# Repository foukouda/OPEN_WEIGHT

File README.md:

<h1 align="center">OPEN_WEIGHT – AD7190</h1>

<p align="center">
  High-precision load-cell / force measurement PCB based on the AD7190
</p>

<p align="center">
  Sub-project of <a href="https://opentruslab.vercel.app/">OPEN THRUST LAB</a>
</p>

<p align="center" width="100%">

</p>

<p align="center">
  
&nbsp; &nbsp; &nbsp; &nbsp;
  
</p>

<p align="center">
  
  <br><sub>Full-resolution video: <a href="Images/OPEN_WEIGHT.mp4">Images/OPEN_WEIGHT.mp4</a> (KiCad raytracing, <code>kicad-cli pcb render</code>)</sub>
</p>

***

## OVERVIEW

**OPEN_WEIGHT** is an open-hardware measurement board developed as part of **OPEN THRUST LAB**, a community-driven project focused on building open-source test benches for drone motor characterization.

This board is designed around the **Analog Devices AD7190**, a high-resolution 24-bit sigma-delta ADC optimized for precision bridge-sensor and load-cell measurements. Within the Open Thrust Lab ecosystem, OPEN_WEIGHT serves as the dedicated **force / thrust measurement interface**, enabling accurate acquisition from load cells for bench instrumentation and motor performance analysis.

The board requires only a **3.3 V input** from the host system. An onboard TPS61086 boost converter steps this up to 6 V, which is then regulated down to a clean +5 V analog supply by an LT3042 ultralow-noise LDO. This two-stage architecture deliberately trades a small efficiency cost for a significantly cleaner AVDD rail, which directly reduces the measurement noise floor. No external 5 V supply is needed.

The repository is structured as a full hardware project rather than a simple PCB dump. It includes:
- KiCad 10 source files for schematic and PCB layout
- **self-contained libraries**: every symbol, footprint and 3D model used on the board lives in `lib/`
- manufacturing and assembly outputs
- generated schematic and fabrication documentation
- validation reports and test artifacts
- 3D views and project visuals
- automated output generation through **KiBot**
- CI integration for reproducible deliverables

OPEN_WEIGHT is meant to be:
- reproducible
- inspectable
- manufacturable
- easy to iterate on
- aligned with open-hardware development practices

***

## PROJECT CONTEXT

OPEN THRUST LAB is an open-source drone motor test-bench initiative covering hardware, firmware, sensors, data, and analysis. Inside this larger architecture, **OPEN-WEIGHT** is the sub-project dedicated to **precision thrust measurement** — an open-source load-cell amplifier and measurement PCB designed for integration into the bench.

In the broader bench roadmap, this board contributes to the measurement chain used to characterize motor performance through reliable sensor acquisition and fully documented hardware design.

***

## DESIGN GOALS

- Provide a precise measurement front-end for load-cell based force sensing
- Operate entirely from a 3.3 V host rail — no external analog supply required
- Support thrust instrumentation in a modular test-bench architecture
- Expose a clean and reusable KiCad 10 project structure
- Automate hardware deliverables with KiBot and CI
- Make fabrication and assembly easier through fully generated outputs
- Support future revisions, validation, and characterization work

***

## SPECIFICATIONS

### Electrical specifications

| Parameter | Value |
| --- | --- |
| Input voltage (VIN) | 3.3 V (from host system) |
| Boost output — TPS61086 | 6 V |
| Analog supply — LT3042 (AVDD) | 5 V, ultralow-noise |
| Digital supply (DVDD) | 3.3 V (from host) |
| ADC | AD7190, 24-bit sigma-delta |
| PGA gain range | 1 – 128 |
| Voltage reference | Ratiometric: REFIN1± = bridge excitation (EXC+/EXC−) — no separate reference IC |
| Digital interface | SPI — Mode 3 (CPOL=1, CPHA=1), max 5 MHz |
| Additional SPI signal | SYNC — filter reset / multi-device synchronization |
| Clock | 4.9152 MHz ceramic resonator (Y2) on MCLK1/MCLK2 |
| Load cell excitation control | Q1 SI2303 P-MOS high-side switch, gate driven by AD7190 **P3** (GPOCON register); low side through **BPDSW** |
| Sensor type | 2 × 4-wire Wheatstone bridge (AIN1/AIN2 and AIN3/AIN4) |
| Full-scale input (gain 128) | ±VREF/128 = ±39 mV with 5 V excitation |

### Power budget

Power chain: **+3.3 V (host) → TPS61086 → +6 V → LT3042 → +5VA → AD7190**

| Stage | Input rail | Typical current | Typical power |
| --- | --- | --- | --- |
| AD7190 analog (AVDD, gain=128, ODR=10 Hz) | +5VA | ~4 mA | ~20 mW |
| Resonator + RC filters + misc analog | +5VA | ~1 mA | ~5 mW |
| Load cell excitation (4-wire bridge, ~350 Ω) | +5VA | ~14 mA | ~70 mW |
| LT3042 quiescent | +6V | ~2 mA | ~12 mW |
| **LT3042 total input load** | **+6V** | **~21 mA** | **~126 mW** |
| AD7190 digital (DVDD) | +3.3V | ~1 mA | ~3.3 mW |
| TPS61086 input (η ≈ 85–90 % at this load) | **+3.3V** | **~45–50 mA** | **~148–165 mW** |
| **Board total estimated** | **+3.3V** | **~46–51 mA** | **~151–168 mW** |

> **Note:** Load cell excitation current depends on bridge resistance. The estimate above assumes a 350 Ω full bridge at 5 V excitation (~14 mA). A 1000 Ω bridge draws ~5 mA instead, reducing total board consumption significantly. TPS61086 efficiency is estimated from the datasheet curve at Vin=3.3 V, Vout=6 V. Always measure at your specific operating point using the **+3.3V** test point TP4 on Page 4.

### Physical specifications

| Parameter | Value |
| --- | --- |
| Project name | OPEN_WEIGHT |
| Board name | AD7190 |
| Parent project | OPEN THRUST LAB |
| CAD tool | KiCad 10 |
| Automation tooling | KiBot + GitHub Actions |
| Dimensions | 54.0 × 48.0 mm |
| Mounting holes | 4× M3, connected to GND |
| Fiducials | Not fitted on this revision (FID1–FID6 excluded from board) |
| Fabrication target | JLCPCB 4-layer, JLC04161H-7628, 1.6 mm (rules in `OPEN_WEIGHT.kicad_dru`) |
| Repository status | In active development |
| Hardware licence | CERN-OHL-P v2 |

***

## SCHEMATIC ARCHITECTURE

The project is organized into four functional hierarchical sheets (under `Project Architecture`), plus the documentation sheets (Revision History, Block Diagram, Power - Sequencing):

| Page | Sheet (file) | Description |
| --- | --- | --- |
| 4 | `AD7190_Weight_Sensor` (`AD7190 - Weight Sensor.kicad_sch`) | AD7190 24-bit sigma-delta ADC front-end for Wheatstone bridge acquisition. Differential inputs on SENSE± and OUT± lines with RC input filtering. SPI interface (CS, DIN, DOUT, SCLK, SYNC). 4.9152 MHz ceramic resonator (Y2). Ratiometric reference REFIN1 = SENSE± (bridge excitation). Dual-supply decoupling (+5VA analog / +3.3V digital). Q1 P-MOS excitation switch driven by AD7190 P3. Test points on all critical analog and digital nodes. |
| 5 | `Power_Supply` (`Power Supply - Analog Rails.kicad_sch`) | Complete analog power chain, +3.3V (host) → +6V → +5VA. **Boost:** TPS61086 at 1.2 MHz (PWM/PFM via MODE, MODE = GND), integrated 2.0 A / 0.13 Ω switch, external Schottky D3, output set by the FB divider R17/R15 (1.238 V × (1 + 69.8k/18k) = 6.04 V), soft-start C18 and compensation R18/C17. **LDO:** LT3042 ultralow-noise LDO (PSRR > 75 dB) from +6V, +5VA set by RSET = 50 kΩ (ISET = 100 µA), solid tantalum C14 = 2.2 µF on SET for noise (soft-start τ = RSET·CSET = 110 ms), Power-Good via the PGFB divider. Test points: +6V (TP11), +5VA (TP10), SET, PGFB, PG, FB, SS, COMP. |
| 6 | `Holes, Fiducials` (`Holes - Fiducials.kicad_sch`) | Mechanical references for PCB fabrication and assembly. Four GND-connected mounting holes (H1–H4, M3). Fiducial symbols FID1–FID6 are kept in the schematic but excluded from the board on this revision. |
| 7 | `Connectors` (`Connectors.kicad_sch`) | External interface connectors for load cell and host communication. Two 5-pin load-cell connectors J2/J4 (21033213501: OUT, OUT, EXC+, EXC−, GND). 7-pin JST-XH host header J1 (+3.3V, CS, DIN, DOUT/RDY, SYNC, SCLK, GND). WE-SHC shielding frame H5 over the analog front-end. |

***

## SIMULATION (LTspice)

The analog power chain and the ADC input filter are simulated with **LTspice 26** in [`Simulation/LTspice/`](Simulation/LTspice). Every component value comes from the KiCad netlist (reference designators are the same as on the schematic), so the schematics can be opened side by side with the KiCad sheets.

| File | Analysis | What it checks |
| --- | --- | --- |
| `01_Power_Chain_Startup.asc` | `.tran` 600 ms, switching | +3.3V → TPS61086 → +6V → LT3042 → +5VA: boost soft-start, inductor current, +5VA settling to 5 V |
| `02_LT3042_Startup.asc` | `.tran` 1 s | +5VA rise, Power-Good, load-cell excitation turn-on (Q1) |
| `03_Power_Ripple.asc` | `.tran` 6 ms, switching | Boost ripple on +6V and what remains on +5VA (waveform and FFT), input current |
| `04_LT3042_PSRR.asc` | `.ac` 10 Hz – 10 MHz | LT3042 ripple rejection with the board's capacitors |
| `05_AD7190_Input_Filter.asc` | `.ac` 10 Hz – 100 MHz | Differential / common-mode response of the AIN RC filter |

**Models**

- **LT3042**: official Analog Devices model shipped with LTspice.
- **TPS61086**: TI does not provide an LTspice model, so `TPS61086_behav.sub` / `.asy` is a **behavioral model** written for this project from the datasheet (SLVSA05B): 1.2 MHz peak-current-mode PWM, gm = 107 µA/V error amplifier, VREF = 1.238 V, 0.13 Ω switch, 2.6 A current limit, 10 µA soft-start, Power Save Mode (MODE = GND, as on the board). The current-sense gain and slope compensation are not published and are estimated.
- **D3**: PMEG2010AEH modelled with the LTspice PMEG2010EA (same 20 V / 1 A Nexperia MEGA Schottky family). **Q1**: approximate VDMOS model of the SI2303CDS.
- Load on +5VA: AD7190 AVDD (4.5 mA) + one 350 Ω bridge + D4 LED. Ceramic capacitors use nominal values (no DC-bias derating).

**Results**

| Quantity | Simulated | Notes |
| --- | --- | --- |
| +6V output (TPS61086) | 6.037 V | FB divider R17/R15, 1.238 V × (1 + 69.8k/18k) |
| +6V reaches 90 % | 1.1 ms | +6V is precharged to ≈ VIN − VF through L1/D3 before the boost starts |
| +6V start-up overshoot | 6.35 V | well within the LT3042 20 V input rating |
| Peak inductor current at start-up | 1.13 A | below the 2.5 A Isat of L1 |
| +6V ripple, 20 MHz bandwidth | 0.7 mV pp | discontinuous conduction at 1.2 MHz, I(L1) peak ≈ 170 mA; the raw trace shows 35 mV single-sample spikes on the switching edges |
| +5VA ripple, 20 MHz bandwidth | < 1 µV pp | 9 µV pp raw, at the numerical resolution of the simulation |
| +6V spectrum, bridge powered | 194 µV rms at 1.2 MHz | FFT of simulation 03: only the switching frequency and its harmonics (78 / 35 / 20 µV rms); 2.8 µV rms in total from 1 kHz to 1 MHz |
| +5VA spectrum, bridge powered | 5.3 nV rms at 1.2 MHz | 91 dB below +6V, in line with the AC analysis below |
| +6V spectrum in standby (Q1 off) | lines from ≈ 90 kHz, up to 115 µV rms | Power Save Mode: the boost only switches in 46 % of the cycles, which spreads the ripple below 1.2 MHz (231 µV rms from 1 kHz to 1 MHz) |
| LT3042 PSRR at 1.2 MHz | 92 dB | ideal layout; real PSRR at MHz is limited by PCB coupling |
| PG goes high | ≈ 5 ms | end of the LT3042 fast start-up (+5VA = 4.59 V) |
| +5VA after 25 ms / 600 ms | 4.645 V / 4.998 V | complete switching chain (01); after the fast start-up +5VA only rises with τ = RSET·CSET = 110 ms, so a short simulation window shows it below 5 V |
| +5VA reaches 99 % / 99.9 % | 241 ms / 494 ms | complete switching chain (01); 248 ms / 501 ms in 02, where the boost is a 12 ms ramp |
| +5VA dip when Q1 turns on | 29 mV | 350 Ω bridge + SENSE± capacitors switched onto +5VA |
| Bridge excitation V(SENSE+) − V(SENSE−) | 4.955 V | Q1 R<sub>DS(on)</sub> + BPDSW drop |
| Input current from the host (+3.3V) | 66.5 mA | includes D1 (≈ 15 mA) and D4 (≈ 5 mA) LEDs |
| Input filter −3 dB, differential | 2.76 kHz | 350 Ω bridge + 2 × 100 Ω, C28 + C27/C29 |
| Input filter −3 dB, common-mode | 57.9 kHz | 175 Ω + 100 Ω, C27/C29 |
| Differential attenuation at 1.2 MHz | −53 dB | boost switching frequency |

**Re-run the simulations** (Windows, LTspice installed in the default location):

```bash
cd Simulation/LTspice
python run_simulations.py              # runs LTspice in batch mode, redraws Images/Simulation/*.png and results.md
python run_simulations.py --only 03 04 # runs only these simulations, then redraws
python run_simulations.py --no-run     # only redraw from the existing .raw files
```

Or open any `.asc` in LTspice and press *Run*. Simulation 03 switches at 1.2 MHz and takes about a minute. Simulation 01 covers 600 ms of 1.2 MHz switching: about 30 minutes and a 2.8 GB `.raw` file (set `.tran 0 25m` to look at the boost soft-start only, about 1 minute).

> The simulations validate the design intent (regulation, sequencing, filtering). They do not replace bench measurements: layout parasitics, capacitor DC-bias derating and the real TPS61086 control loop will change the ripple figures.

***

## LAYOUT COUPLING (openEMS)

The routed copper is simulated with the **openEMS 0.0.36** field solver (FDTD) in [`Simulation/openEMS/`](Simulation/openEMS), to find what the boost stage leaves on the AD7190 inputs through the layout itself. The four copper layers are taken from the KiCad board and one source of the boost stage is driven at a time:

| Drive | Source | Result |
| --- | --- | --- |
| `sw` | Switch node voltage (IC2 pin 6) | Mutual capacitance to each analog net |
| `loop` | Current of the commutation loop IC2 – D3 – C19/C20 | Mutual inductance to the connector tracks, the input filter and the ADC pins |
| `input` | Current of the input loop C21/C22 – L1 – IC2 | Same |
| `coil` | Current loop of the size of L1, at its place | Same, for the stray field of the inductor |

Each drive is run on the bare board and with the WE-SHC shield H5 fitted with its cover (the frame alone only for the `sw` drive). `measurement_quality.py` then puts these couplings together with the waveforms of LTspice simulation 03 (V(SW) and I(L1), bridge powered) and with the input filter read from the board (R1/R2/R4/R5, C6/C8/C10, C27/C28/C29, a 350 Ω load cell on each connector). The result is the voltage left between the two pins of each ADC input.

**Results**

Worst case: the AD7190 samples its inputs at 307.2 kHz (MCLK / 16) and its digital filter does not reject what falls on a multiple of that rate. 4 × 307.2 kHz = 1.229 MHz is inside the tolerance of the TPS61086 oscillator, so nothing is credited to the digital filter. Away from such a coincidence the digital filter removes the switching frequency altogether.

| Between the two pins of the input, at 1.2 MHz | Bare board | Shield H5 with its cover |
| --- | --- | --- |
| Channel 1 (J4), switch node voltage | 0.04 nV rms | 0.004 nV rms |
| Channel 1 (J4), boost current loops | 3.7 nV rms | 15 nV rms |
| Channel 2 (J2), switch node voltage | 0.2 nV rms | 0.06 nV rms |
| Channel 2 (J2), boost current loops | 38 nV rms | 15 nV rms |
| Reference input (REFIN1), all together | 95 nV rms | 29 nV rms |
| For comparison: noise of the AD7190 itself (4.7 Hz, gain 128) | 8.5 nV rms | 8.5 nV rms |

- Capacitive coupling from the switch node is negligible: 0.006 to 0.06 fF to each analog net on the bare board.
- The path that counts is magnetic. The current loops of the boost stage induce a voltage in the small loop between the capacitor across each pair (C6, C28) and the ADC pins, behind the filter, and around the two capacitors to ground (C8/C10, C27/C29).
- 15 nV is 1.5 ppm of what a 2 mV/V load cell gives at full load under 5 V, and less than twice the noise of the AD7190 itself.
- On the bare board channel 1 (J4) is ten times less exposed than channel 2 (J2), which sits on the side of the boost stage.
- With the cover both channels end up at the same level. What remains comes from the input loop; how it gets under the cover is not identified.
- The reference input sees more, but the reading is a ratio to it: 95 nV on 5 V is 19 ppb.
- L1 is a shielded inductor and its stray field is not published, so it is only bounded, all of its stored energy being taken as stray field: at most 0.9 µV (channel 1) and 2.7 µV (channel 2) on the bare board, 18 nV and 220 nV with the cover. The bound goes with the square root of the share of energy that really leaks. This is the reason to fit the cover.
- Every harmonic up to 250 MHz taken together gives 140 nV (channel 1) and 730 nV (channel 2) on the bare board, 26 nV and 72 nV with the cover. This is a ceiling: the input stage of the AD7190 does not follow tens of MHz, and the LTspice switch commutates in no time.
- A 0.15 mm mesh instead of 0.2 mm changes the commutation loop result by −5 % on channel 1 and +27 % on channel 2.

The complete tables are in [`Simulation/openEMS/results.md`](Simulation/openEMS/results.md).

<p align="center">
  
  <br><sub>Field over time: <a href="Images/Simulation/openems_sw_efield.mp4">Images/Simulation/openems_sw_efield.mp4</a></sub>
</p>

**Re-run the simulation** (Windows, openEMS and its Python 3.11 environment installed in `C:\openEMS`):

```bash
cd Simulation/openEMS
"C:\Program Files\KiCad\10.0\bin\python.exe" export_kicad_geometry.py   # copper of the board -> geometry.json
C:\openEMS\venv\Scripts\python.exe sw_coupling.py --check               # mesh the board and verify the nets
C:\openEMS\venv\Scripts\python.exe sw_coupling.py --case open           # the four drives on the bare board
C:\openEMS\venv\Scripts\python.exe sw_coupling.py --case shield         # the same with the cover
C:\openEMS\venv\Scripts\python.exe measurement_quality.py               # results.md and the figure
```

One run meshes 1.85 M cells and takes about 13 minutes on 8 cores. `measurement_quality.py` needs the `.raw` file of LTspice simulation 03.

> Not modelled: the load cell and its cable, the connectors above the board, the package of the AD7190. Fitted parts are wires at the mid height of their body and the boost waveforms come from a behavioral model, so expect a factor 2 to 3 on these figures. A bench measurement of the ADC noise with the boost running and stopped remains the reference.

***

## LOAD CELL CONNECTION

The board accepts any standard **4-wire Wheatstone bridge** load cell.

### Load-cell connectors J2 / J4 (21033213501, 5 pins)

| Pin | Net (J4 / J2) | Function |
| --- | --- | --- |
| 1 | IN-OUT+ / IN-OUT+2 | Bridge signal output (through 100 Ω + RC filter) |
| 2 | IN-OUT− / IN-OUT−2 | Bridge signal output (through 100 Ω + RC filter) |
| 3 | SENSE+ | Excitation + (switched +5VA from Q1) and REFIN1(+) |
| 4 | SENSE− | Excitation − (AD7190 BPDSW low-side switch) and REFIN1(−) |
| 5 / shell | GND | Cable shield |

J4 → AIN1/AIN2, J2 → AIN3/AIN4. Both channels measure **V(pin 2) − V(pin 1)**: if the load reads negative, swap the signal wires or invert the sign in firmware.

> ⚠️ Load cell cable colors vary by manufacturer. Always verify EXC± and SIG± with a multimeter **before** powering the board.

> ⚠️ The excitation is switched by **Q1 (P-MOS)** whose gate is driven by the AD7190 **P3** pin. Enable it through the GPOCON register (GP32EN = 1, P3DAT = 0 → Q1 on). Do not enable excitation during internal calibration.

### Compatible load cell characteristics

- Differential output: **0 – 20 mV/V** at rated excitation
- Bridge resistance: **120 Ω to 1000 Ω** full bridge
- Ratiometric measurement: with gain 128 and 5 V excitation, full-scale input = ±5 V / 128 = **±39 mV**

### Host header J1 (JST-XH B7B-XH-AM, 7 pins)

| Pin | Signal | Direction | Notes |
| --- | --- | --- | --- |
| 1 | +3.3V | Power in | Board supply (boost input + AD7190 DVDD) |
| 2 | CS | Input | Active low (100 kΩ pull-up R8) |
| 3 | DIN | Input | Serial data to AD7190 (100 Ω series, RN1) |
| 4 | DOUT/RDY | Output | Serial data from AD7190; also goes low when a conversion is ready |
| 5 | SYNC | Input | Active low — resets the digital filter; tie high if unused |
| 6 | SCLK | Input | SPI clock, max 5 MHz |
| 7 | GND | — | Common ground |

> ⚠️ SPI Mode 3 only (CPOL=1, CPHA=1). There is no separate DRDY pin: poll DOUT/RDY with CS low.

***

## STARTUP SEQUENCE

After 3.3 V is applied, allow the following stages to complete before issuing any SPI command
(see schematic page 8, *Power - Sequencing*; values from the [LTspice simulations](#simulation-ltspice)):

| Stage | Duration | Indicator |
| --- | --- | --- |
| TPS61086 boost start-up (C18 soft-start) | +6V at 90 % after ~1.1 ms, settled after ~2 ms (short 6.35 V overshoot) | +6V reaches 6.04 V (TP11) |
| LT3042 fast start-up (2 mA into CSET while PGFB < 300 mV) | +5VA reaches 4.59 V after ~5 ms | PG (TP17) goes high at 4.59 V |
| LT3042 final settling (RSET 50 kΩ × CSET 2.2 µF = τ 110 ms) | 99 % after ~250 ms, 99.9 % after ~500 ms | +5VA (TP10) |
| **Minimum safe delay** | **≥ 600 ms** from power-on | +5VA settled |

> PG goes high long before +5VA is settled: it only indicates the end of the fast start-up phase. Use the delay, not PG, before calibrating.

> To start faster, reduce C14 (e.g. 0.47 µF → τ = 23.5 ms) at the cost of slightly higher low-frequency noise.

After the delay, the recommended initialization sequence is:

```
1. Issue AD7190 serial reset: assert CS̄, write 40+ bytes of 0xFF on DIN
2. Write CONF register (gain, reference, chop settings)
3. Write MODE register (filter, ODR)
4. Run internal zero-scale calibration — wait for DRDȲ
5. Run internal full-scale calibration — wait for DRDȲ
6. Enable load cell excitation: GPOCON GP32EN=1, P3DAT=0 (Q1 on)
7. Run system calibration with known reference weight
8. Enter continuous conversion mode
```

***

## CALIBRATION

Two levels of calibration are required. Both must be repeated after every power cycle.

### 1. Internal calibration

Corrects the ADC's own offset and gain. Requires no external weights. Must be re-run after any change to PGA gain or ODR.

```
Write MODE register: MD[2:0] = 0b001  (internal zero-scale)
→ Wait for DRDȲ to go low

Write MODE register: MD[2:0] = 0b010  (internal full-scale)
→ Wait for DRDȲ to go low

Results are saved in the ZERO and FULLSCALE registers.
Read them back to cache for faster subsequent startups.
```

### 2. System calibration

Maps ADC output codes to physical units. Repeat any time the mechanical setup changes.

```
1. Remove all load → average ≥16 samples → raw_zero
2. Apply known weight W_ref → average ≥16 samples → raw_full
3. scale_factor = W_ref / (raw_full − raw_zero)
4. weight = (raw_code − raw_zero) × scale_factor
```

### Recommended register configuration

| Register | Field | Value | Reason |
| --- | --- | --- | --- |
| `CONF` | GAIN[2:0] | `0b111` (128×) | Maximizes resolution for low-sensitivity load cells |
| `CONF` | REFSEL | `0b0` | REFIN1± = bridge excitation (ratiometric) |
| `CONF` | CHOP | `1` | Reduces offset and drift |
| `MODE` | SINC | `0b11` (SINC4) | Best 50/60 Hz rejection |
| `MODE` | FS[9:0] | `0x1E0` (480) | fADC = 4.9152 MHz / (1024 × FS) ≈ 10 Hz without chop — rejects 50/60 Hz (with CHOP=1 the rate is lower, see datasheet) |

> ⚠️ After any change to GAIN, ODR, or filter settings, the sigma-delta pipeline resets. Always re-run internal calibration before taking measurements.

> ⚠️ At gain 128 with the 5 V ratiometric reference: full-scale input range = **±39 mV**. A 2 mV/V load cell at 5 V gives 10 mV at full load.

***

## HOW TO USE

### Prerequisites

- **KiCad 10** (files are saved in KiCad 10 format and cannot be opened with KiCad 9 or earlier)
- Nothing else: all symbols, footprints and 3D models are in `lib/` and referenced relative to the project (`KIPRJMOD`, project-local `sym-lib-table` / `fp-lib-table`)
- **KiBot** for automated output generation
- **Docker** recommended for reproducible local CI runs
- Debian/Ubuntu or equivalent environment

### Generate outputs locally

```bash
# Default configuration
./kibot_launch.sh

# Specific variant
./kibot_launch.sh -v CHECKED
```

| Variant | Outputs | ERC/DRC | Typical use |
| --- | --- | --- | --- |
| `DRAFT` | Schematic only | — | Early design work |
| `PRELIMINARY` | Schematic + PCB | — | Layout iterations |
| `CHECKED` | Full | ✓ enforced | Design review, PR validation |
| `RELEASED` | Full | ✓ enforced | Tagged version releases |

### Use a manufactured board

```c
// --- After >= 600 ms from 3.3V power-on (LT3042 soft-start, see page 8) ---

// 1. Reset
ad7190_reset();                            // 40× 0xFF on DIN

// 2. Configure
ad7190_write_reg(REG_CONF,
    CONF_GAIN_128 | CONF_CHOP | CONF_REFSEL_REFIN1);
ad7190_write_reg(REG_MODE,
    MODE_SINC4 | MODE_FS_10HZ);

// 3. Internal calibration
ad7190_write_reg(REG_MODE, MODE_INT_ZERO_CAL);
while (drdy_is_high());
ad7190_write_reg(REG_MODE, MODE_INT_FULL_CAL);
while (drdy_is_high());

// 4. Enable load cell excitation
ad7190_write_reg(REG_GPOCON, GPOCON_GP32EN); // P3 = 0 -> Q1 on

// 5. System calibration
uint32_t raw_zero = ad7190_average(16);    // No load
apply_reference_weight();
uint32_t raw_full = ad7190_average(16);
float scale = W_ref / (float)(raw_full - raw_zero);

// 6. Continuous measurement
ad7190_write_reg(REG_MODE, MODE_CONTINUOUS);
while (1) {
    while (drdy_is_high());
    uint32_t raw = ad7190_read_data();
    float weight = (raw - raw_zero) * scale;
}
```

***

## REPOSITORY CONTENT

| Content | Description |
| --- | --- |
| Schematic sources | KiCad hierarchical schematic — 10 sheets |
| PCB layout | KiCad PCB with all production layers |
| Manufacturing | Gerbers, drill tables, BoM, pick-and-place files |
| Validation | ERC/DRC reports, test-point tables |
| 3D exports | STEP files and rendered views |
| Documentation sheets | Block diagram, architecture, power sequencing, revision history |
| CI resources | GitHub Actions workflows, KiBot YAML configurations |
| Computations | Design notes, filter and power budget calculations |
| Simulation | LTspice simulations of the power chain and ADC input filter, openEMS simulation of the layout coupling |

***

## DIRECTORY STRUCTURE

    .
    ├─ Computations       # Design notes, formulas, and power budget calculations
    ├─ HTML               # Generated HTML pages and web outputs
    ├─ Images             # Pictures, renders, and visual assets
    │
    ├─ kibot_resources    # External resources used by KiBot
    │  ├─ colors          # Color themes for KiCad outputs
    │  ├─ fonts           # Fonts used in generated documents
    │  ├─ scripts         # Helper scripts used with KiBot
    │  └─ templates       # Templates for KiBot reports and generated outputs
    │
    ├─ kibot_yaml         # KiBot YAML configuration files
    ├─ KiRI               # KiRI PCB diff viewer files
    │
    ├─ lib                # Project libraries (self-contained)
    │  ├─ lib_sym         # OPEN_WEIGHT.kicad_sym — every symbol used
    │  ├─ lib_fp          # OPEN_WEIGHT.pretty — every footprint used
    │  └─ 3d_models       # STEP models referenced by the footprints
    │
    ├─ Logos              # Project logos and branding assets
    │
    ├─ Manufacturing
    │  ├─ Assembly        # BoM, position files, assembly notes
    │  └─ Fabrication     # Gerbers, drill tables, fabrication notes
    │     ├─ Drill Tables
    │     └─ Gerbers
    │
    ├─ Mechanical         # Enclosure / support CAD (STEP; SolidWorks & STL kept local)
    ├─ Report             # ERC / DRC reports and validation outputs
    ├─ Schematic          # Exported schematic PDFs
    ├─ Simulation
    │  ├─ LTspice         # LTspice schematics, TPS61086 behavioral model, run/plot script
    │  └─ openEMS         # Field-solver model of the routed copper, coupling to the ADC inputs
    ├─ Templates          # Drawing sheets and title block templates
    ├─ Testing
    │  └─ Testpoints      # Test point tables and documentation
    │
    └─ Variants           # Outputs for project / assembly variants

***

## DEVELOPMENT WORKFLOW

This project uses a reproducible hardware workflow based on **KiCad 10**, **KiBot**, and **GitHub Actions**.

The CI pipeline (`.github/workflows/ci.yaml`) runs KiBot on every push to `dev` or `main` and commits the generated outputs back ("Update Outputs" commits). **Always `git pull` after the CI has run, before editing the project again**, otherwise the regenerated files (`.kicad_pro`, BoM, netlist, README…) will conflict.

> ℹ️ `README.md` is **generated** by KiBot from `kibot_resources/templates/readme.txt`. Edit the template, not `README.md`, or your changes will be overwritten by the next CI run.

**Branch convention:**
- `dev` — development branch, all work branches off here
- Feature branches: `feat/description`
- Fix branches: `fix/description`
- `main` — only receives merges from `dev`; releases are tagged here

**Project metadata** (project name, board name, company, designer, logo, repository URL) is defined once in `kibot_yaml/kibot_main.yaml` (`definitions:` section) and propagated to title blocks, documents and this README.

**Release a new hardware revision:**

1. On `dev`, fill the `[Unreleased]` section of [CHANGELOG.md](CHANGELOG.md) (Added / Changed / Fixed / Removed).
2. Merge `dev` into `main`: `git checkout main && git pull && git merge dev && git push`
3. Tag with a plain semantic version (**no `v` prefix**, the CI only matches `X.Y.Z`): `git tag 1.0.0 && git push origin 1.0.0`
4. The CI builds the `RELEASED` variant, publishes a GitHub Release with fabrication files, and moves `[Unreleased]` to the new version in `CHANGELOG.md`.
5. Re-sync `dev`: `git checkout main && git pull && git checkout dev && git merge main`

***

## TROUBLESHOOTING

| Symptom | Likely cause | Fix |
| --- | --- | --- |
| Output stuck at 0 or inverted | EXC± wiring error | Verify bridge polarity with multimeter |
| Output always at full-scale | SIG+ / SIG− swapped | Swap the two signal wires |
| Garbage SPI readings | SPI mode mismatch | Set host to Mode 3 (CPOL=1, CPHA=1) |
| Readings drift over time | No internal cal after power-on | Re-run zero-scale + full-scale internal calibration |
| DOUT/RDY never goes low | Resonator not oscillating | Reflow Y2 (4.9152 MHz resonator) |
| SPI reads 0xFF | CS̄ stuck high or SCLK too fast | Check CS̄ GPIO; reduce SCLK to ≤ 5 MHz |
| 50/60 Hz interference | ODR too high or wrong filter | Use SINC4 + FS = 0x00A (10 Hz ODR) |
| +5VA absent at power-on | TPS61086 not switching | Verify +3.3V_IN; check inductor L1 solder joints |
| +5VA present but noisy | LT3042 SET pin cap issue | Reflow solid tantalum cap on SET pin (Page 5) |
| No excitation on load cell | Q1 off | Write GPOCON: GP32EN = 1, P3DAT = 0 |
| First readings drift for ~0.5 s | +5VA still rising (τ = 110 ms) | Wait ≥ 600 ms after power-up before calibration |
| Offset drifts after warmup | Thermal settling | Allow 5–10 min warmup; re-tare before measurements |

***

## CONTRIBUTING

Contributions are welcome — hardware corrections, documentation improvements, firmware examples, and validation reports all add value to the project.

### Requirements

- **KiCad 10** — not backwards-compatible with earlier versions
- Respect existing layer naming, reference designator conventions, and title block format
- All hardware contributions must pass ERC and DRC under the `CHECKED` variant

### Workflow

1. Fork the repository
2. Create a branch off `dev`: `feat/your-description` or `fix/your-description`
3. Make your changes
4. Run `./kibot_launch.sh -v CHECKED` — resolve all ERC/DRC violations
5. Open a Pull Request against `dev` with a clear description of the change and its rationale

### Reporting issues

Open a GitHub Issue and include:
- Board revision (from silkscreen or revision history sheet)
- Photos or annotated screenshots of the affected area
- Symptom and conditions under which it occurs
- ERC/DRC report if design-related

***

## CHANGELOG

See [CHANGELOG.md](CHANGELOG.md) for the full board revision history following [Keep a Changelog](https://keepachangelog.com/) conventions with semantic versioning.

***

## LICENSE

Hardware design files in this repository are released under the **CERN Open Hardware Licence Version 2 – Permissive (CERN-OHL-P v2)**.

See [LICENSE](LICENSE) for the full licence text.

Under CERN-OHL-P v2:
- You may use, study, modify, and manufacture this design freely
- Derivative works do **not** need to remain open-source
- Modified files must carry a notice identifying the changes made and their author
- The original copyright and attribution notice must be preserved

> For more on CERN-OHL licences: [ohwr.org/cern_ohl](https://ohwr.org/cern_ohl)

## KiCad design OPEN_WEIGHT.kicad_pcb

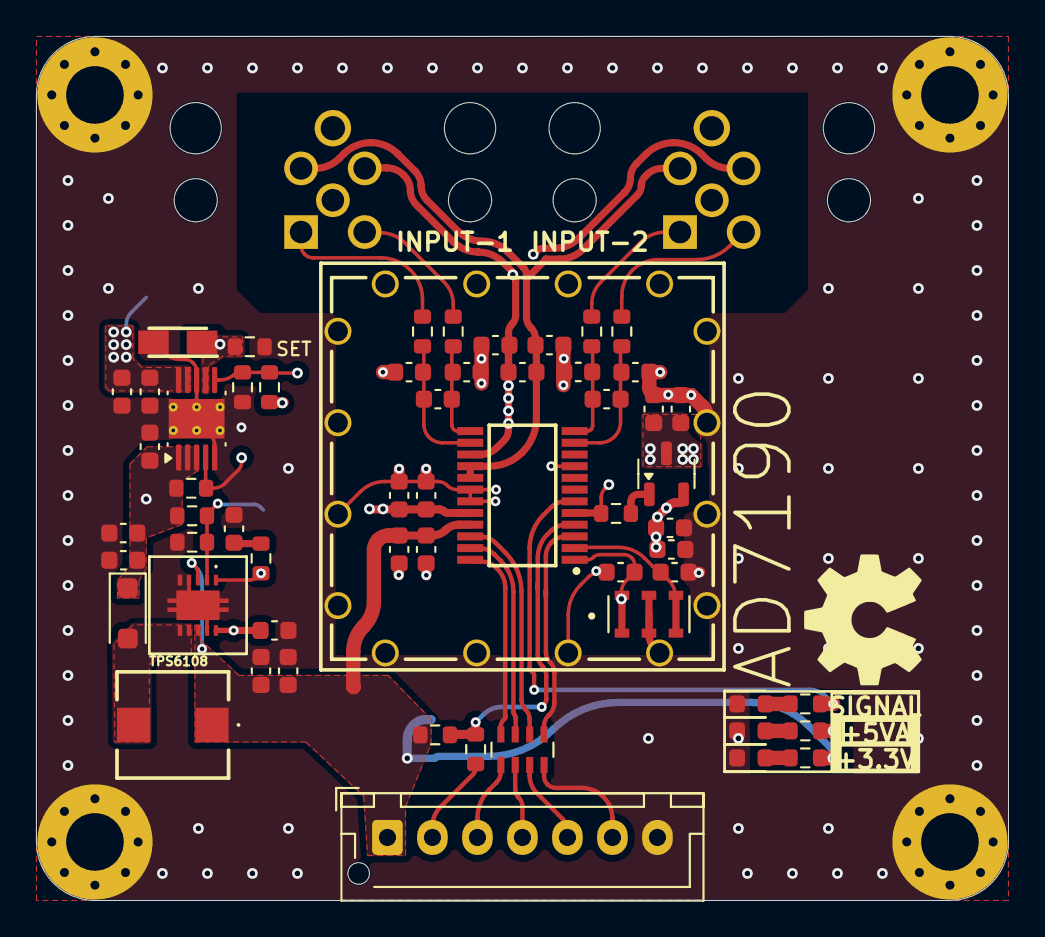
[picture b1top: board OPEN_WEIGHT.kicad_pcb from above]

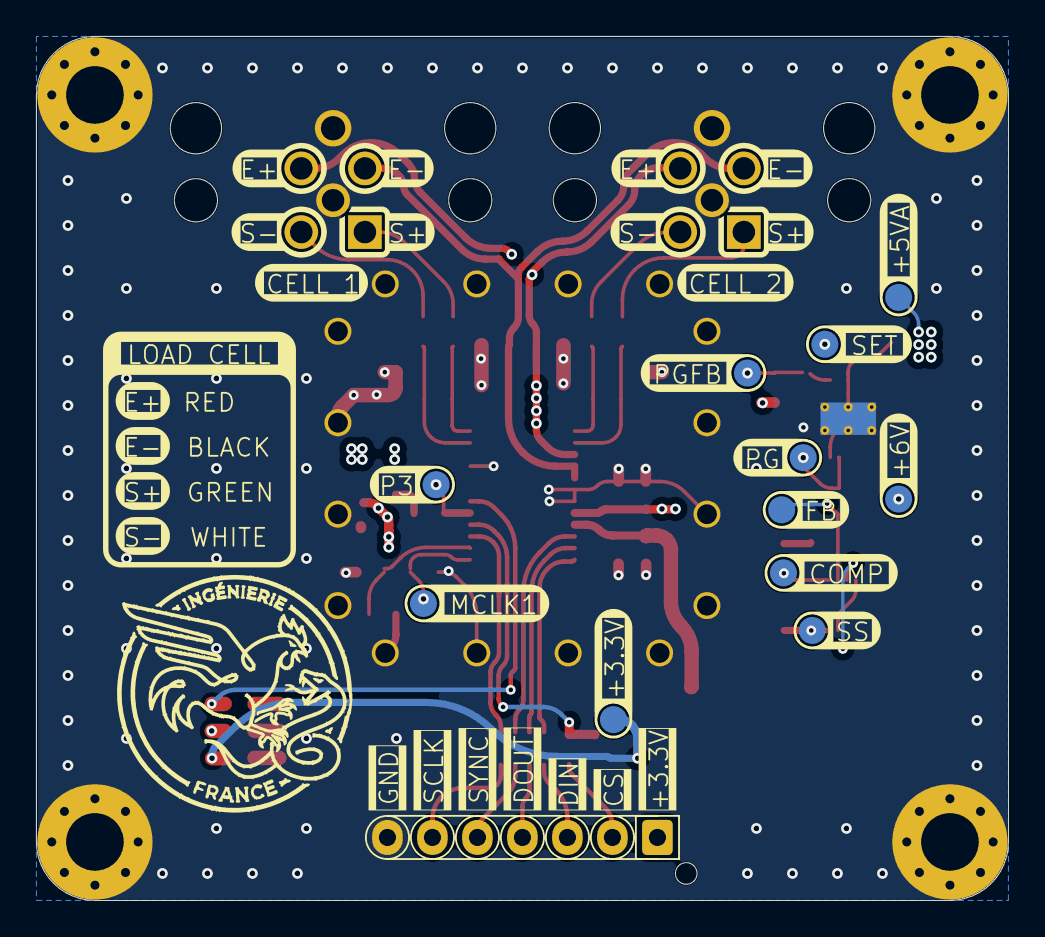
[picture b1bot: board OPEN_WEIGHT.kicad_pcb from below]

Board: 4 copper layers, 54.0 x 48.0 mm, 76 parts (11 on the bottom side), 40 nets.

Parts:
C1, C3, C5, C6, C11, C23, C26, C28: 0.1µF; C_0603_1608Metric
C2, C4, C12, C15, C19, C20, C21: 10µF; C_0603_1608Metric
C7, C8, C9, C10, C27, C29: 0.01µF; C_0603_1608Metric
C13, C16: 4.7µF; C_0603_1608Metric
C14: TAJA225K016RNJ; CAPPM3216X180N
C17: 2.2nF; C_0603_1608Metric
C18: 0.1uF; C_0603_1608Metric
C22: 1µF; C_0603_1608Metric
C24, C25: 18pf; C_0603_1608Metric
D1, D4: LED; LED_0603_1608Metric
D2: RED; LED_0603_1608Metric
D3: PMEG2010AEH; D_SOD-123F
H1, H2, H3, H4: MountingHole_Pad; MountingHole_3.2mm_M3_Pad_Via
H5: WE-SHC_THT-FRAME; WE-SHC_THT-FRAME_36503205
IC2: TPS61086DRCR; TPS16412DRCR
J1: Conn_01x07_Pin; JST_XH_B7B-XH-AM_1x07_P2.50mm_Vertical
J2, J4: 21033213501
L1: 7447785004
Q1: SI2303CDS-T1-GE3; SOT-23-3
R1, R2, R3, R4, R5, R6, R11: 100Ω; R_0603_1608Metric
R8: 100kΩ; R_0603_1608Metric
R9, R13: 50kΩ; R_0603_1608Metric
R10: 1kΩ; R_0603_1608Metric
R12: 715kΩ; R_0603_1608Metric
R14: 200kΩ; R_0603_1608Metric
R15: 18kΩ; R_0603_1608Metric
R16: 620Ω; R_0603_1608Metric
R17: 69.8kΩ; R_0603_1608Metric
R18: 37.4kΩ; R_0603_1608Metric
RN1: RP_100Ω; R_Array_Concave_4x0603
TP2, TP4, TP5, TP11, TP12, TP13, TP14, TP15, TP16, TP17, TP18: TestPoint; TestPoint_Pad_D1.5mm
U1: AD7190WBRUZ; SOP65P640X120-24N
U2: LT3042IMSE; MSOP-10-1EP_3x3mm_P0.5mm_EP2.2x3.1mm_Mask1.83x1.89mm_Therma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
Y2: CSTCR4M91G53-R0; OSC_CSTCR4M91G53-R0

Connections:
+3.3V: C1.1, C2.1, C21.1, C22.1, IC2.3 (EN), IC2.8 (IN), J1.1, L1.1, R3.2, R8.1, TP4.1, U1.21 (DVDD)
+5VA: C3.2, C4.2, C12.1, C13.1, C15.1, C26.1, Q1.2 (S), R12.2, R16.2, TP5.1, U1.20 (AVDD), U2.9 (OUTS), U2.10 (OUT)
+6V: C16.1, C19.1, C20.1, D3.1 (K), R14.1, R17.2, TP11.1, U2.1 (IN), U2.2 (IN), U2.3 (EN/UV)
/Project Architecture/Power_Supply/COMP: IC2.1 (COMP), R18.2, TP16.1
/Project Architecture/Power_Supply/FB: IC2.2 (FB), R15.2, R17.1, TP14.1
/Project Architecture/Power_Supply/PG: R14.2, TP17.1, U2.4 (PG)
/Project Architecture/Power_Supply/PGFB: R12.1, R13.2, TP13.1, U2.6 (PGFB)
/Project Architecture/Power_Supply/SET: C14.1 (+), R9.2, TP12.1, U2.7 (SET)
/Project Architecture/Power_Supply/SS: C18.1, IC2.10 (SS), TP15.1
CS: J1.2, R6.1
DIN: J1.3, RN1.5 (R4.2)
DOUT: J1.4, RN1.6 (R3.2)
GND: C1.2, C2.2, C3.1, C4.1, C7.1, C8.2, C9.2, C10.1, C11.2, C12.2, C13.2, C14.2 (-), C15.2, C16.2, C17.2, C18.2, C19.2, C20.2, C21.2, C22.2, C23.2, C24.2, C25.2, C26.2, C27.1, C29.2, D1.1 (K), D2.1 (K), D4.1 (K), H1.1, H2.1, H3.1, H4.1, H5.1, H5.2, H5.3, H5.4, H5.5, H5.6, H5.7, H5.9, H5.10, H5.11, H5.12, H5.13, H5.14, H5.15, H5.16, H5.17, IC2.4 (AGND), IC2.5 (PGND), IC2.9 (MODE), IC2.11 (EP), IC2.12 (EP_2), IC2.13 (EP_3), IC2.14 (EP_4), IC2.15 (EP_5), J1.7, J2.5, J2.S1 (SHIELD), J4.5, J4.S1 (SHIELD), R9.1, R13.1, R15.1, U1.9 (NC), U1.18 (AGND), U1.19 (DGND), U2.5 (ILIM), U2.8 (GND), U2.11 (GND), Y2.2
IN-OUT+: J4.1, R4.1
IN-OUT+2: J2.1, R2.1
IN-OUT-: J4.2, R5.1
IN-OUT-2: J2.2, R1.1
MCLK1: C25.1, TP2.1, U1.1 (MCLK1), Y2.1
MCLK2: C24.1, U1.2 (MCLK2), Y2.3
unnamed: C17.1, R18.1
unnamed: D1.2 (A), R3.1
unnamed: D2.2 (A), R11.2
unnamed: D3.2 (A), IC2.6 (SW_1), IC2.7 (SW_2), L1.2
unnamed: D4.2 (A), R16.1
unnamed: Q1.1 (G), R10.2
unnamed: RN1.1 (R1.1), U1.3 (SCLK)
unnamed: RN1.2 (R2.1), U1.22 (~SYNC)
unnamed: RN1.3 (R3.1), U1.23 (DOUT/~RDY)
unnamed: RN1.4 (R4.1), U1.24 (DIN)
unnamed: R11.1, U1.6 (P2)
unnamed: R6.2, R8.2, U1.4 (~CS)
OUT+: C27.2, C28.1, R4.2, U1.12 (AIN2)
OUT+2: C6.1, C10.2, R1.2, U1.13 (AIN3)
OUT-: C28.2, C29.1, R5.2, U1.11 (AIN1)
OUT-2: C6.2, C8.1, R2.2, U1.14 (AIN4)
P3: R10.1, TP18.1, U1.5 (P3)
SCLK: J1.6, RN1.8 (R1.2)
SENSE+: C5.1, C7.2, C11.1, C23.1, J2.3, J4.3, Q1.3 (D), U1.15 (REFIN1(+))
SENSE-: C5.2, C9.1, J2.4, J4.4, U1.16 (REFIN1(-)), U1.17 (BPDSW)
SYNC: J1.5, RN1.7 (R2.2)

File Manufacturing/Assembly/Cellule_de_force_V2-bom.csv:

Row,Quantity Per PCB,References,Value,Datasheet,Footprint,Description,Manufacturer,Manufacturer Part Number,Supplier Part Number
1,2,C11 C12,22pf,~,C_0603_1608Metric,Unpolarized capacitor,,,
2,1,C17,2.2nF,~,C_0603_1608Metric,Unpolarized capacitor,,,
3,4,C7 C8 C9 C10,0.01µF,~,C_0603_1608Metric,Unpolarized capacitor,,,
4,5,C1 C3 C5 C6 C18,0.1µF,~,C_0603_1608Metric,Unpolarized capacitor,,,
5,1,C22,1µF,~,C_0603_1608Metric,Unpolarized capacitor,,,
6,2,C13 C16,4.7µF,~,C_0603_1608Metric,Unpolarized capacitor,,,
7,6,C2 C4 C15 C19 C20 C21,10µF,~,C_0603_1608Metric,Unpolarized capacitor,,,
8,1,C14,TAJA225K016RNJ,http://www.farnell.com/datasheets/1680476.pdf,CAPPM3216X180N,"TAJ SMT tant capacitor,Case A,16V,2.2uF AVX 2.2uF SMD Solid MnO2 Tantalum Electrolytic Capacitor, 16 V dc +/-10%, TAJ Series",,,
9,3,D1 D2 D4,LED,~,LED_0603_1608Metric,Light emitting diode,,,
10,1,D3,PMEG2010AEH,https://assets.nexperia.com/documents/data-sheet/PMEG2010AEH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,D_SOD-123F,"20V, 1A very low Vf MEGA Schottky barrier rectifier, SOD-123F",,,
11,1,IC2,TPS61086DRCR,https://www.ti.com/lit/gpn/TPS61086,TPS16412DRCR,Switching Voltage Regulators 18.5V PFM/PWM Step- Up DC-DC Converter,,,
12,6,J1 J2 J3 J4 J5 J6,Conn_01x02_Pin,~,PinHeader_1x02_P2.54mm_Vertical,"Generic connector, single row, 01x02, script generated Generic connector, single row, 01x04, script generated Generic connector, single row, 01x05, script generated",,,
13,1,L1,7447785004,https://www.we-online.com/catalog/datasheet/7447785004.pdf,7447785004,WE-PD Robust SMT Shielded Power Inductor Size 6033; L = 4.7 H ; IR = 2.65 A; Isat = 2.5 A; RDC = 78 m,,,
14,9,R1 R2 R3 R4 R5 R6 R7 R10 R11,100Ω,~,R_0603_1608Metric,Resistor,,,
15,1,R16,620Ω,~,R_0603_1608Metric,Resistor,,,
16,1,R15,18kΩ,~,R_0603_1608Metric,Resistor,,,
17,1,R18,37.4kΩ,~,R_0603_1608Metric,Resistor,,,
18,2,R9 R13,50kΩ,~,R_0603_1608Metric,Resistor,,,
19,1,R17,69.8kΩ,~,R_0603_1608Metric,Resistor,,,
20,1,R8,100kΩ,~,R_0603_1608Metric,Resistor,,,
21,1,R14,200kΩ,~,R_0603_1608Metric,Resistor,,,
22,1,R12,715kΩ,~,R_0603_1608Metric,Resistor,,,
23,1,U1,AD7190WBRUZ,,SOP65P640X120-24N,,Analog Devices,,
24,1,U2,LT3042IMSE,https://www.analog.com/media/en/technical-documentation/data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,MSOP-10-1EP_3x3mm_P0.5mm_EP2.2x3.1mm_Mask1.83x1.89mm_ThermalVias,"200mA, Adjustable, Ultralow Noise, Ultrahigh PSRR RF Linear Regulator, MSOP-10",,,
25,1,Y1,ABC2-4.9152MHZ-4-T,https://abracon.com/Resonators/abc2.pdf,ABC210000MHZ4,LOW FREQUENCY CERAMIC SURFACE MOUNT MICROPROCESSOR CRYSTAL,,,

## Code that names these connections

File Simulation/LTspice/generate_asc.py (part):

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    c17 = s.part("cap", "A", (704, 560), "C17", "2.2n")
    s.wire(r18["B"], c17["A"])
    s.gnd(c17["B"])
    s.label((752, 400), "COMP")
    s.label(r18["B"], "CC")
    s.wire(ic["SS"], (848, 432), (912, 432))
    c18 = s.part("cap", "A", (912, 432), "C18", "0.1u")
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    s.gnd(r9["B"])
    c14 = s.part("polcap", "A", (1744, 400), "C14", "2.2u", spiceline="Rser=3")
    s.gnd(c14["B"])
    s.label((1840, 400), "SET")
    s.text(1664, 560, "C14 = TAJA225K016 (tantalum)", 1)
    s.gnd(u2["GND"], 48)
    s.gnd(u2["ILIM"], 48)
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    s.wire(r12["B"], (2528, 288), r13["A"])
    s.gnd(r13["B"])
    s.wire(u2["PGFB"], (2256, 384), (2448, 384), (2448, 288), (2528, 288))
    s.label((2448, 288), "PGFB")
    s.wire(u2["OUTS"], (2400, 224), (2400, Y5))
    rail5 = [u2["OUT"][0], 2400, 2464, 2528]
    x = 2656
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
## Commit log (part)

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2026-02-22 Update Outputs
2026-02-23 [Schématique test]
2026-02-24 [FINISH LT3042 and ad TPS6108]
2026-02-24 [ADD TPS6108]
2026-02-25 [Finish schématique]
2026-02-25 [Finish schématiq]
2026-02-27 [PCB fini]
2026-02-27 [PCB 2]
2026-02-27 [PCB 3]
2026-02-27 [PCB 4]
2026-02-27 [PCB 5]
2026-02-27 [PCB 6]
2026-03-10 [PCB 4 layer]
2026-03-12 [PCB V1]
2026-03-13 [PCB V2]
2026-03-13 Revise README with project details and structure
    Updated project title and added overview, context, design goals, specifications, and development workflow sections.
2026-03-13 Enhance README with badges and detailed sections
    Added license and status badges to README, improved specifications and troubleshooting sections.
2026-03-13 Enhance README.md for better project documentation
    Update README.md with improved clarity and detail on project specifications, calibration, and usage instructions.
2026-03-14 [PCB V3]
2026-03-14 Revise README with project details and specifications
    Updated project title and added detailed project overview, context, design goals, specifications, and usage instructions.
2026-03-16 [PCB V4]
2026-03-16 Revise project title and add overview details
    Updated project name and description in README.md
2026-03-18 [PCB FINAL]
2026-03-18 [PCB FINA]
2026-03-21 [PCB FIN]
2026-03-21 [PCB FI]

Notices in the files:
README.md:
License: CERN-OHL-P v2
